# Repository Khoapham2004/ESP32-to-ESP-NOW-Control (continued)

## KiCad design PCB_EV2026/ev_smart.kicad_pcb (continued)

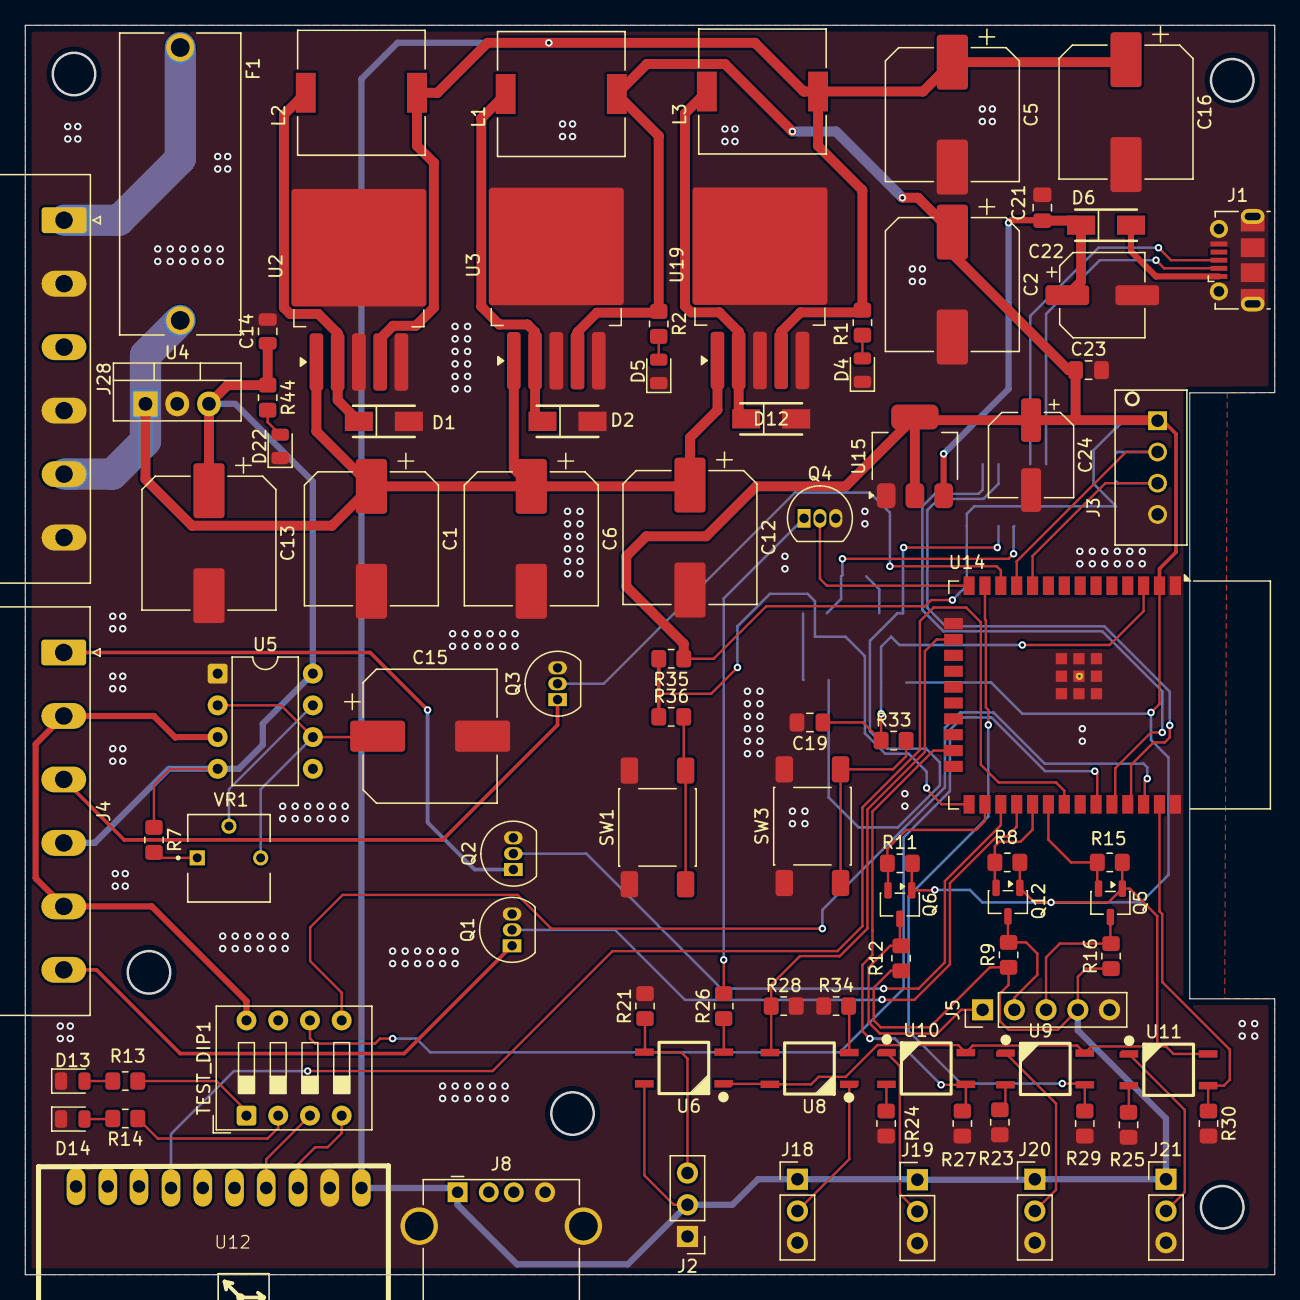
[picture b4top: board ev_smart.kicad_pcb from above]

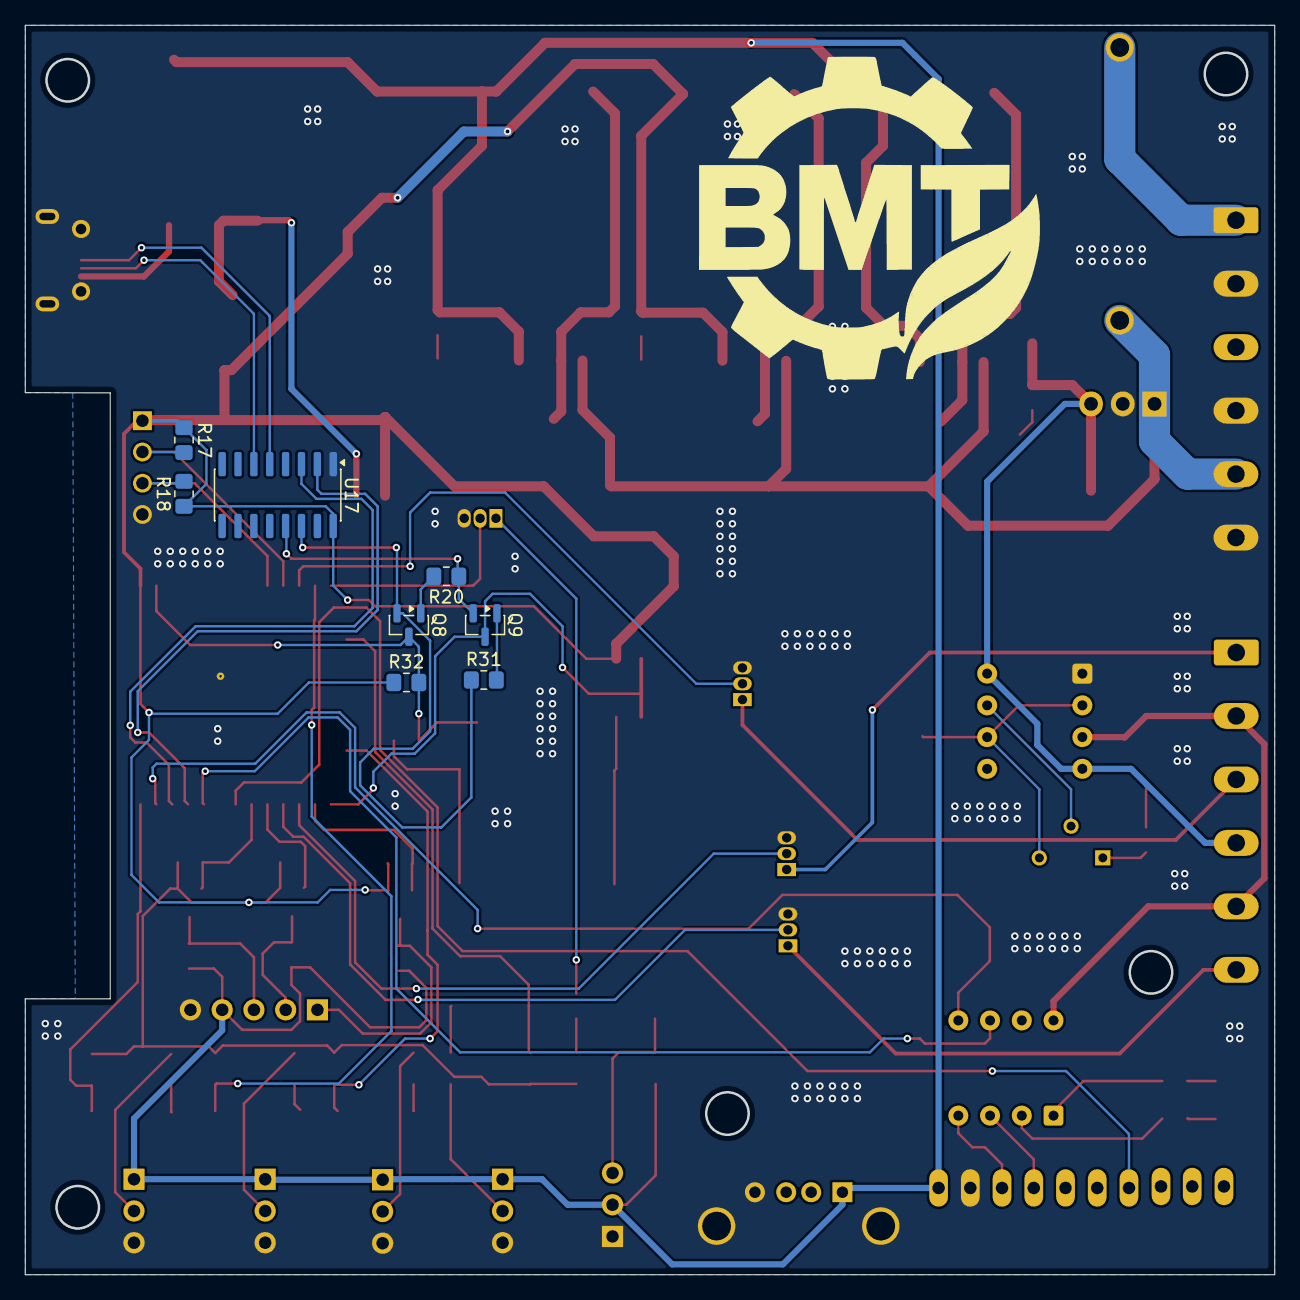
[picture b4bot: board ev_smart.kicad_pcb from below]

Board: 2 copper layers, 99.9 x 99.8 mm, 95 parts (8 on the bottom side), 69 nets.

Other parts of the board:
J28: Screw_Terminal_01x06; PhoenixContact_MSTBA_2,5_6-G-5,08_1x06_P5.08mm_Horizontal

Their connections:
/DC-DC/PowerBTS: J28.5; also elsewhere on the board
/DC-DC/PowerIN: J28.1; also elsewhere on the board
GND: J28.2, J28.4, J28.6; also elsewhere on the board

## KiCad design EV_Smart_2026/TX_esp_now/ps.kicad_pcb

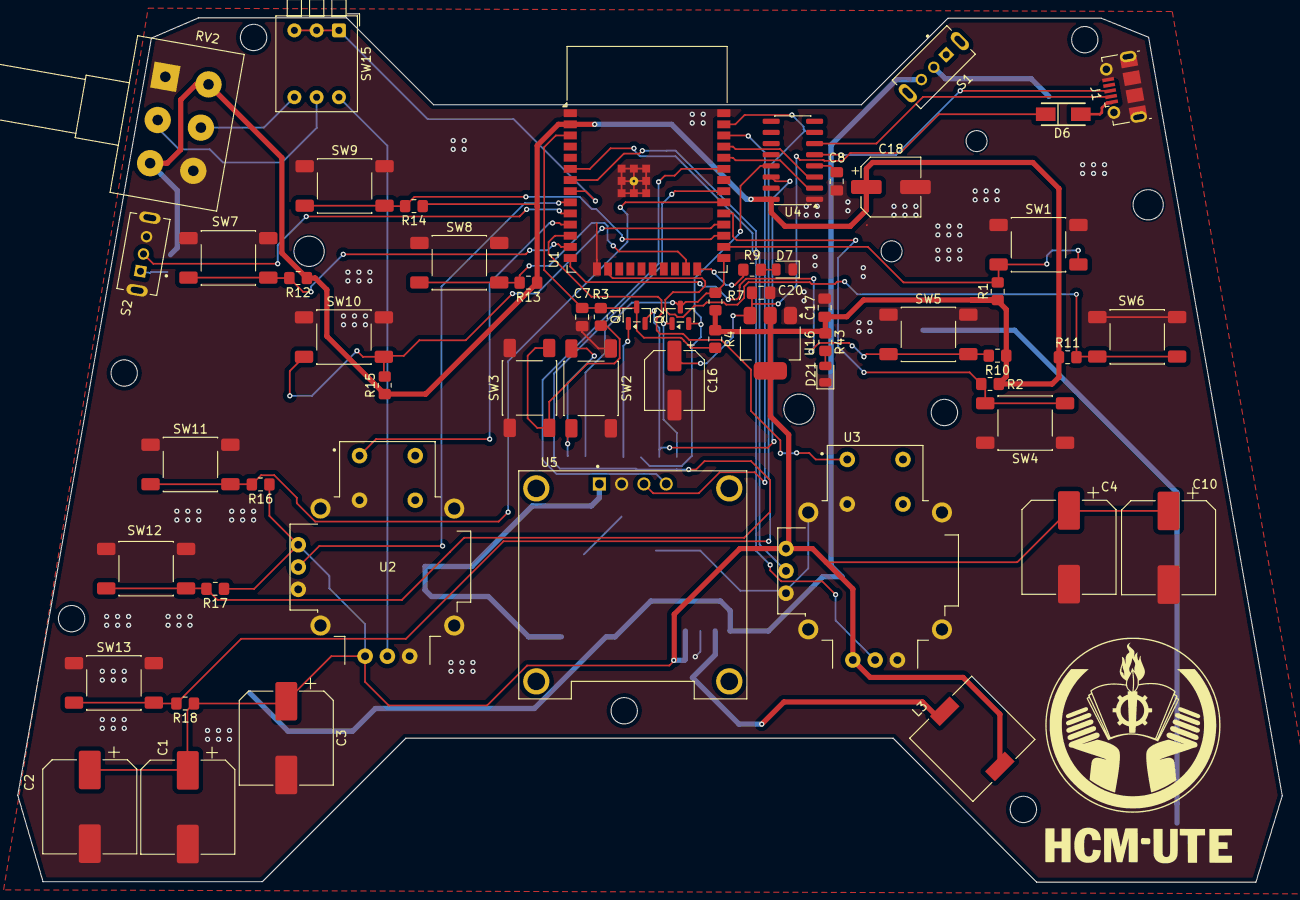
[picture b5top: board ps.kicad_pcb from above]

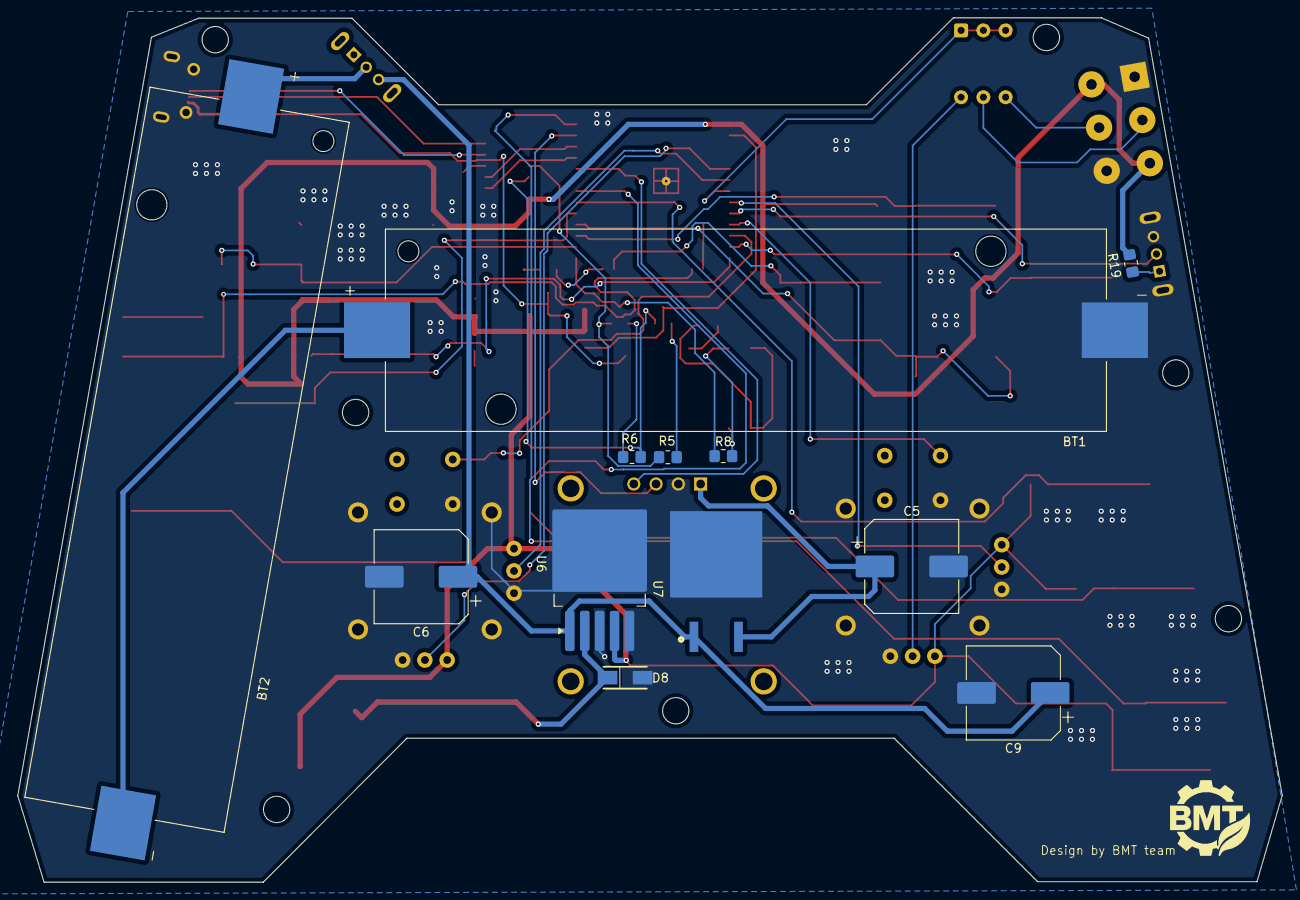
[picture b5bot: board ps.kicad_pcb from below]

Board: 2 copper layers, 144.1 x 98.5 mm, 69 parts (12 on the bottom side), 49 nets.

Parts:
BT1, BT2: 1122; BAT_1122
C1, C2, C3, C4, C5, C10: 220uF/50V; CP_Elec_10x10.5
C6, C9: 470uF/50V; CP_Elec_10x10.5
C7: 10uF; C_0805_2012Metric_Pad1.18x1.45mm_HandSolder
C8, C17, C20: 1uF; C_0805_2012Metric_Pad1.18x1.45mm_HandSolder
C16, C18: 100uF; CP_Elec_6.3x5.4
D6, D8: SS54-HF; DIOM5025X220N
D7, D21: LED; LED_0805_2012Metric
J1: USB_B_Micro; USB_Micro-B_Molex-105017-0001
L3: CDRH105RNP-4R7NC; IND_CDRH105RNP-4R7NC
Q1, Q2: BC847; SOT-23
R1, R2, R10, R11, R12, R13, R14, R15, R16, R17, R18, R19: 1k; R_0805_2012Metric_Pad1.20x1.40mm_HandSolder
R3, R8: 470; R_0805_2012Metric_Pad1.20x1.40mm_HandSolder
R4, R7: 12k; R_0805_2012Metric_Pad1.20x1.40mm_HandSolder
R5, R6: 10k; R_0805_2012Metric_Pad1.20x1.40mm_HandSolder
R9, R43: 330; R_0805_2012Metric_Pad1.20x1.40mm_HandSolder
RV2: R_Potentiometer_Dual; Potentiometer_Alps_RK163_Dual_Horizontal
S1, S2: SS12D07VG4; SW_SS12D07VG4
SW1, SW2, SW3, SW4, SW5, SW6, SW7, SW8, SW9, SW10, SW11, SW12, SW13: SW_Push; SW_Push_1P1T_NO_E-Switch_TL3301NxxxxxG
SW15: SW_DIP_x03; SW_DIP_SPSTx03_Piano_10.8x9.18mm_W7.62mm_P2.54mm
U1: ESP32-WROOM-32D
U2, U3: COM-09032; XDCR_COM-09032
U4: CH340C; SOIC-16_3.9x9.9mm_P1.27mm
U5: DM-OLED096-636; MODULE_DM-OLED096-636
U6: LM2596S-3.3; TO-263-5_TabPin3
U7: L7805; TO254P1515X470-3N
U16: AMS1117-3.3; SOT-223-3_TabPin2

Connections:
+3.3V: C1.1, C2.1, C3.1, C4.1, C10.1, C17.1, C18.1, L3.2, R1.1, R2.1, R4.1, R7.1, R10.1, R11.1, R12.1, R13.1, R14.1, R15.1, R16.1, R17.1, R18.1, R19.1, R43.1, RV2.3, RV2.4, U1.2 (VDD), U2.H1 (H+), U2.V1 (V+), U3.H1 (H+), U3.V1 (V+), U4.16 (VCC), U6.4 (FB), U16.2 (VO)
+5V: C5.1, U5.2 (VCC_IN), U7.3 (OUT)
/INTPUT_DATA/ADC32: SW15.1, SW15.2, SW15.3, U1.8 (IO32)
/INTPUT_DATA/B1: R1.2, SW1.2, U1.26 (IO4)
/INTPUT_DATA/B2: R2.2, SW4.2, U1.29 (IO5)
/INTPUT_DATA/B3: R10.2, SW5.2, U1.14 (IO12)
/INTPUT_DATA/B4: R11.2, SW6.2, U1.16 (IO13)
/INTPUT_DATA/B5: R12.2, SW7.2, U1.13 (IO14)
/INTPUT_DATA/B6: R13.2, SW8.2, U1.23 (IO15)
/INTPUT_DATA/B7: R14.2, SW9.2, U1.27 (IO16)
/INTPUT_DATA/B8: R15.2, SW10.2, U1.28 (IO17)
/INTPUT_DATA/B9: R16.2, SW11.2, U1.30 (IO18)
/INTPUT_DATA/B10: R17.2, SW12.2, U1.31 (IO19)
/INTPUT_DATA/B11: R18.2, SW13.2, U1.37 (IO23)
/INTPUT_DATA/B12: S2.2, U1.10 (IO25)
/INTPUT_DATA/JSW1: U1.11 (IO26), U2.B1A (SEL+)
/INTPUT_DATA/JSW2: U1.12 (IO27), U3.B1A (SEL+)
/INTPUT_DATA/POT1: RV2.2, SW15.5
/INTPUT_DATA/POT2: RV2.5, SW15.4
/INTPUT_DATA/SCL_esp32: U1.36 (IO22), U5.3 (SCL)
/INTPUT_DATA/SDA_esp32: U1.33 (IO21), U5.4 (SDA)
/INTPUT_DATA/Vrx1: SW15.6, U2.H2 (H)
/INTPUT_DATA/Vrx2: U1.6 (IO34), U3.H2 (H)
/INTPUT_DATA/Vry1: U1.9 (IO33), U2.V2 (V)
/INTPUT_DATA/Vry2: U1.7 (IO35), U3.V2 (V)
/esp32/EN: C7.1, Q1.3 (C), R3.1, R4.2, U1.3 (EN)
/esp32/IO0: Q2.3 (C), R7.2, R8.1, U1.25 (IO0)
/esp32/IO2: R9.1, U1.24 (IO2)
D+: J1.3 (D+), U4.5 (UD+)
D-: J1.2 (D-), U4.6 (UD-)
DTR: Q2.2 (E), R5.1, U4.13 (~DTR)
GND: BT1.N, C1.2, C2.2, C3.2, C4.2, C5.2, C6.2, C7.2, C8.2, C9.2, C10.2, C16.2, C17.2, C18.2, C20.2, D7.1 (K), D8.2, D21.1 (K), J1.5 (GND), J1.6 (Shield), RV2.1, RV2.6, S2.3, S2.S1 (SHIELD), S2.S2 (SHIELD), SW1.1, SW2.1, SW3.1, SW4.1, SW5.1, SW6.1, SW7.1, SW8.1, SW9.1, SW10.1, SW11.1, SW12.1, SW13.1, U1.1 (GND), U1.15 (GND), U1.38 (GND), U1.39 (GND), U2.B2A (SEL-), U2.H3 (H-), U2.S1 (SHIELD), U2.S2 (SHIELD), U2.S3 (SHIELD), U2.S4 (SHIELD), U2.V3 (V-), U3.B2A (SEL-), U3.H3 (H-), U3.S1 (SHIELD), U3.S2 (SHIELD), U3.S3 (SHIELD), U3.S4 (SHIELD), U3.V3 (V-), U4.1 (GND), U5.1 (GND), U6.3 (GND), U6.5 (~ON/OFF), U7.2 (GND), U16.1 (GND)
unnamed: BT1.P, BT2.N
unnamed: BT2.P, S1.2
unnamed: D7.2 (A), R9.2
unnamed: D21.2 (A), R43.2
unnamed: D6.2, J1.1 (VBUS)
unnamed: Q1.1 (B), R5.2
unnamed: Q2.1 (B), R6.2
unnamed: R3.2, SW3.2
unnamed: R8.2, SW2.2
unnamed: R19.2, S2.1
unnamed: C8.1, U4.4 (V3)
unnamed: D8.1, L3.1, U6.2 (OUT)
unnamed: C6.1, C9.1, S1.3, U6.1 (VIN), U7.1 (IN)
unnamed: C16.1, C20.1, D6.1, U16.3 (VI)
RTS: Q1.2 (E), R6.1, U4.14 (~RTS)
RX0: U1.34 (RXD0/IO3), U4.2 (TXD)
TX0: U1.35 (TXD0/IO1), U4.3 (RXD)

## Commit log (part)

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2025-05-10 Rename Kẻ điên thiếu ngủ (@useri4uil) - TikTok.mp4 to Autodriving-pythone.mp4
2025-06-09 Create test
2025-06-09 Rename test to image_processing.py
2025-07-04 Rename esp32_recv.ino to esp32_recv1.ino
2025-07-04 Rename sketch_jun13a.ino to esp_ok.ino
2025-07-15 Rename esp_now_trans.ino to esp_now_trans.cpp
2025-07-15 Rename MainCode/Auto_Driving_pythone/Readme.md to MainCode/Readme.md
2025-07-15 Rename MainCode/Get_ID_esp32.cpp to MainCode/ESP_NOW_CONTROL/Get_ID_esp32.cpp
2025-07-15 Rename MainCode/Readme.md to MainCode/ESP_NOW_CONTROL/Readme.md
2025-07-15 Rename MainCode/esp_now_receive.cpp to MainCode/ESP_NOW_CONTROL/esp_now_receive.cpp
2025-07-15 Rename MainCode/esp_now_trans.cpp to MainCode/ESP_NOW_CONTROL/esp_now_trans.cpp
2025-07-15 Rename Autodriving-pythone.mp4 to MainCode /Auto_Driving_pythone/Autodriving-pythone.mp4
2025-07-15 Rename MainCode /Auto_Driving_pythone/Autodriving-pythone.mp4 to MainCode/Auto_Driving_pythoneAutodriving-pythone.mp4
2025-07-15 Rename MainCode/Auto_Driving_pythoneAutodriving-pythone.mp4 to MainCode/Auto_Driving_pythone/REVUARRT.inoAuto_Driving_pythoneAutodriving-pythone.mp4
2025-07-15 Rename video.mp4 to MainCode/ESP_NOW_CONTROL/Get_ID_esp32.cppvideo.mp4
2025-07-15 Rename video (2).mp4 to video.mp4
